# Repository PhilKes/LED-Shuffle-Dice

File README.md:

# LED Shuffle Dice
### Attiny85 with Shiftregister and Accelerometer
#### Parts
* Attiny85 Microcontroller
* **74HC595** Shiftregister
* 7 **Red LEDs**
* Coin Cell Battery + Holder
* ADXL345 Accelerometer
#### Schematic

* Minimal I/O Pins required (in total: 4)
* 2 Pin Connection to Shiftregister (CLK and DATA to **Attiny85** + LATCH connected to DATA)
* Accelerometer for Shake Detection
* "Shuffle" Animation
* LEDs logically connected in Pairs

#### 3D Printed Case

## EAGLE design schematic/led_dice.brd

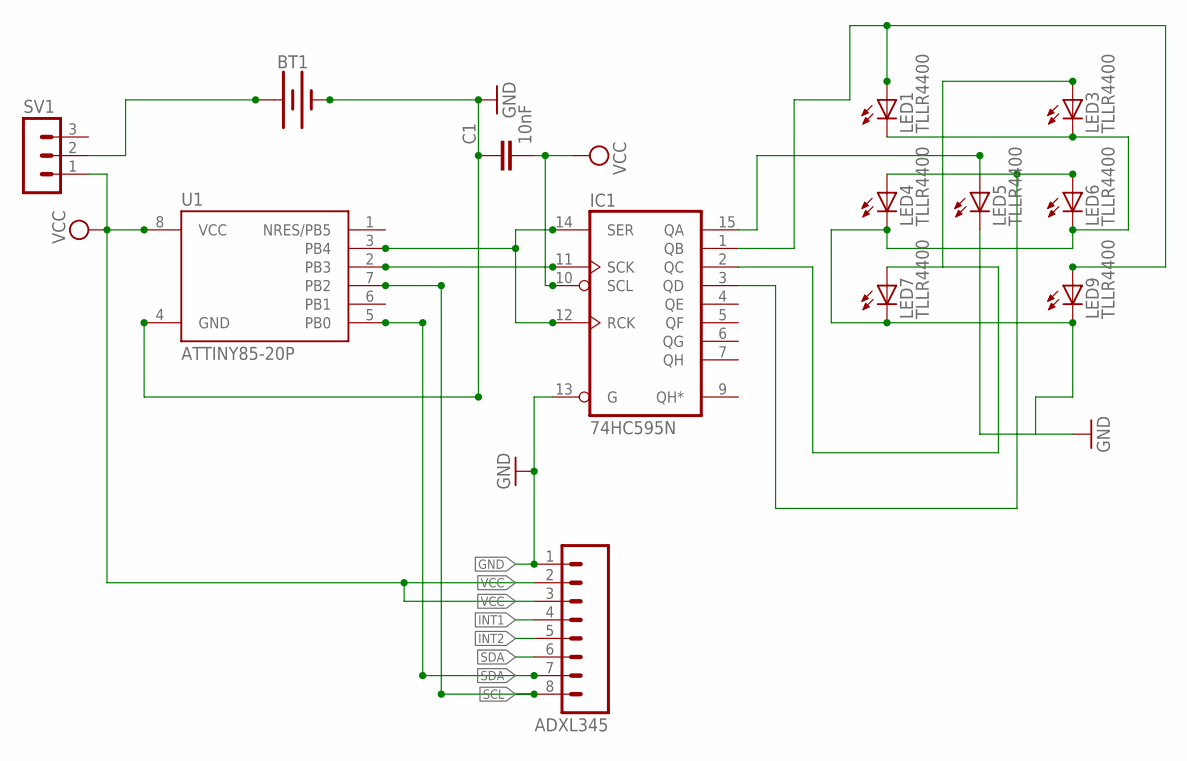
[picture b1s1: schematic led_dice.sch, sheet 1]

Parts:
ADXL345: M08; 1X08
BT1: BATTERY-20MM_PTH; BATTCOM_20MM_PTH
C1: 10nF; C025-024X044
IC1: 74HC595N; DIL16
LED1, LED3, LED4, LED5, LED6, LED7, LED9: TLLR4400; LED3MM
SV1: MA03-1
U1: ATTINY85-20P; PDIP08_300MIL

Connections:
GND: ADXL345.1, BT1.2 (-), C1.1, IC1.8 (GND), IC1.13 (G), LED1.K (C), LED3.K (C), LED4.K (C), LED5.K (C), LED6.K (C), LED7.K (C), LED9.K (C), U1.4 (GND)
INT1: ADXL345.4
INT2: ADXL345.5
unnamed: IC1.1 (QB), LED1.A, LED9.A
unnamed: IC1.15 (QA), LED5.A
unnamed: IC1.11 (SCK), U1.2 (PB3)
unnamed: IC1.3 (QD), LED4.A, LED6.A
unnamed: BT1.1 (+), SV1.2
unnamed: IC1.2 (QC), LED3.A, LED7.A
unnamed: IC1.12 (RCK), IC1.14 (SER), U1.3 (PB4)
SCL: ADXL345.8, U1.7 (PB2)
SDA: ADXL345.7, U1.5 (PB0)
VCC: ADXL345.2, ADXL345.3, C1.2, IC1.10 (SCL), IC1.16 (VCC), SV1.1, U1.8 (VCC)

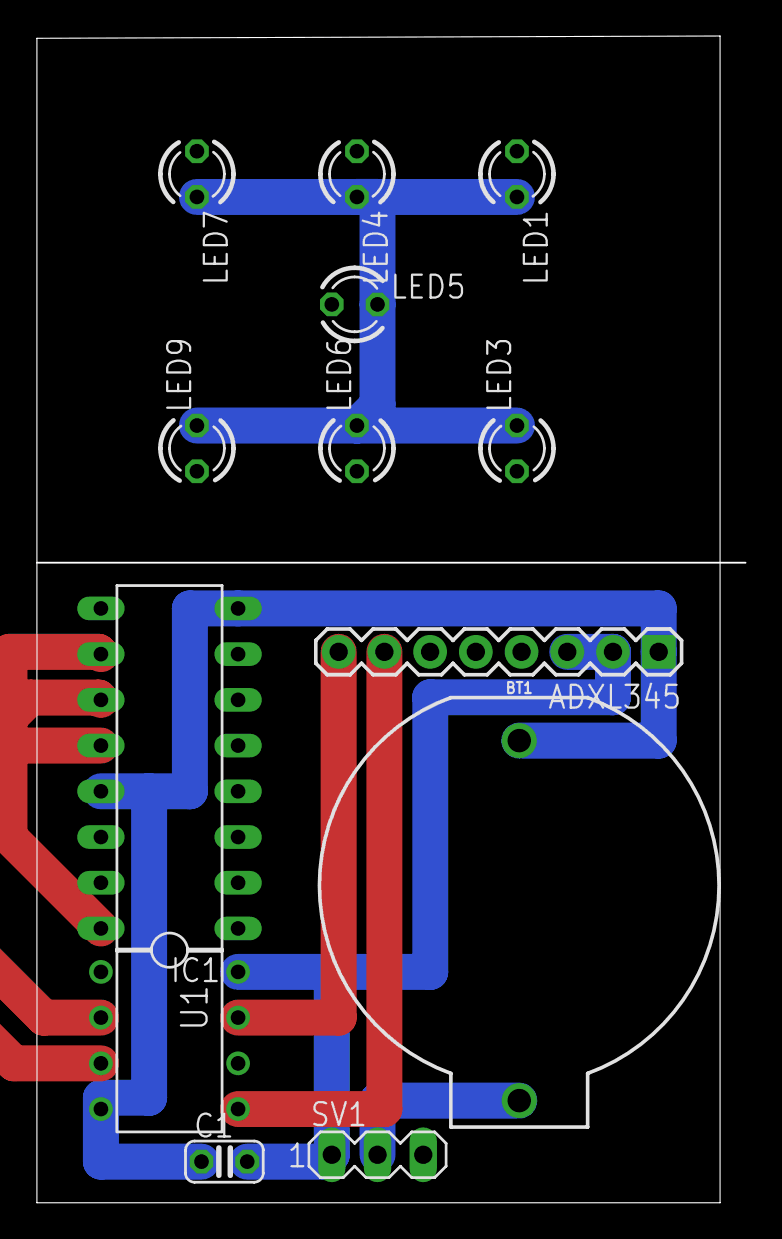
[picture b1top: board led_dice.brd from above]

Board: 2 copper layers, 39.4 x 64.7 mm, 13 parts (0 on the bottom side), 11 nets.

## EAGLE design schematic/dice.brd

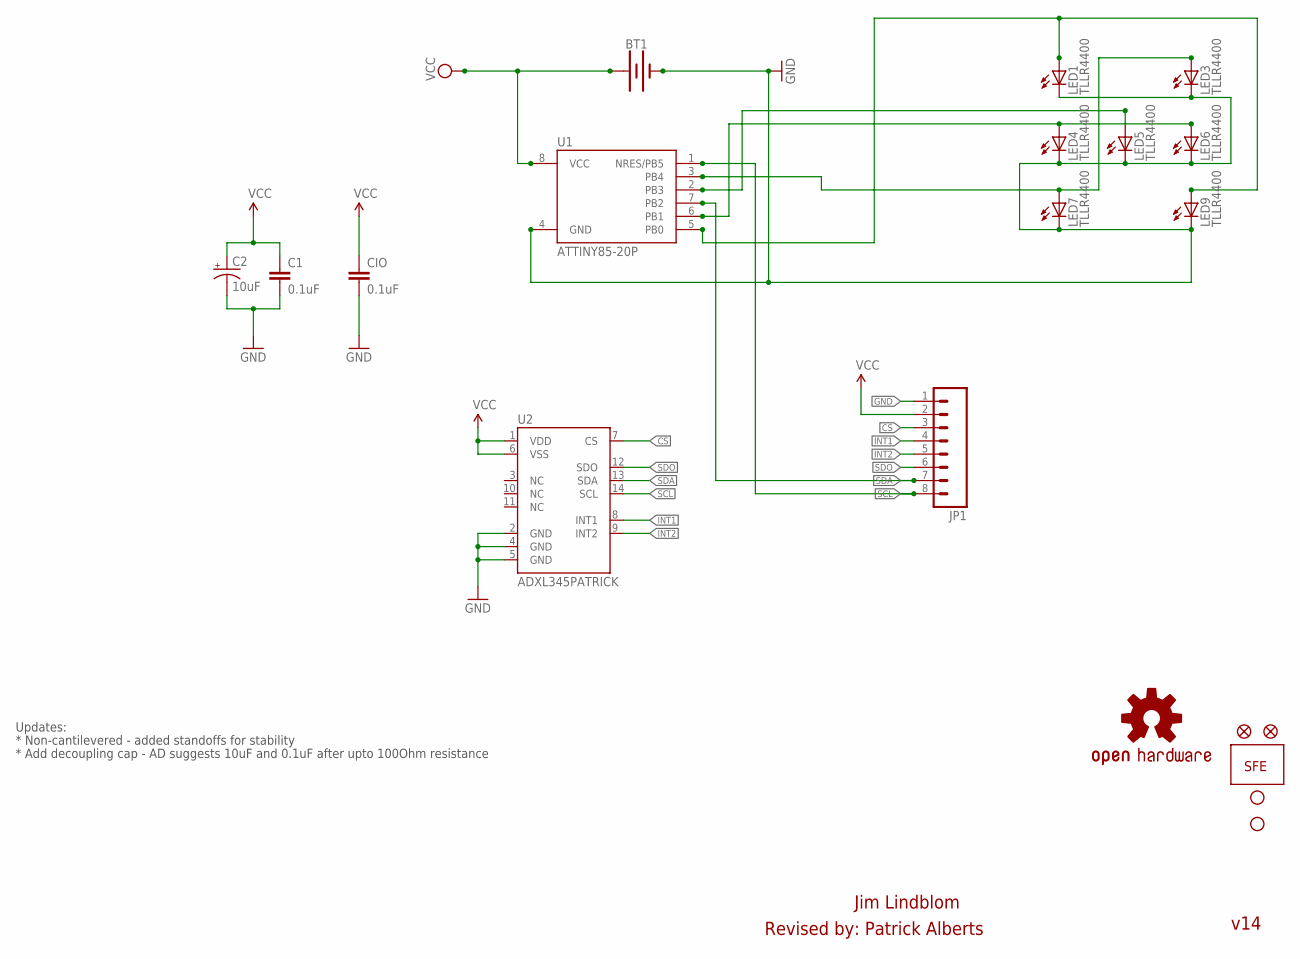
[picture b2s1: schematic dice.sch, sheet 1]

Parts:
BT1: BATTERY-20MM_PTH; BATTCOM_20MM_PTH
C1: 0.1uF; 0603-CAP
C2: 10uF; EIA3216
CIO: 0.1uF; 0603-CAP
JP1: M08; 1X08
JP2, JP3: STAND-OFF
JP4, JP5: FIDUCIAL1X2; FIDUCIAL-1X2
LED1, LED3, LED4, LED5, LED6, LED7, LED9: TLLR4400; LED3MM
U1: ATTINY85-20P; PDIP08_300MIL
U2: ADXL345PATRICK; LGA14_1:1_PATRICK
U$2: LOGO-SFENEW; SFE-NEW-WEBLOGO
U$3: OSHW-LOGOS; OSHW-LOGO-S

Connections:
CS: JP1.3, U2.7 (CS)
GND: BT1.2 (-), C1.2, C2.C (-), CIO.2, JP1.1, LED1.K (C), LED3.K (C), LED4.K (C), LED5.K (C), LED6.K (C), LED7.K (C), LED9.K (C), U1.4 (GND), U2.2 (GND), U2.4 (GND), U2.5 (GND)
INT1: JP1.4, U2.8 (INT1)
INT2: JP1.5, U2.9 (INT2)
unnamed: LED1.A, LED9.A, U1.5 (PB0)
unnamed: LED3.A, LED7.A, U1.3 (PB4)
unnamed: LED5.A, U1.2 (PB3)
unnamed: LED4.A, LED6.A, U1.6 (PB1)
SCL: JP1.8, U1.1 (NRES/PB5), U2.14 (SCL)
SDA: JP1.7, U1.7 (PB2), U2.13 (SDA)
SDO: JP1.6, U2.12 (SDO)
VCC: BT1.1 (+), C1.1, C2.A (+), CIO.1, JP1.2, U1.8 (VCC), U2.1 (VDD), U2.6 (VSS)

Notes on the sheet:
Updates:
* Non-cantilevered - added standoffs for stability
* Add decoupling cap - AD suggests 10uF and 0.1uF after upto 100Ohm resistance
Jim Lindblom
Revised by: Patrick Alberts
v14

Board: 2 copper layers, 20 parts (0 on the bottom side), 12 nets, no tracks yet.

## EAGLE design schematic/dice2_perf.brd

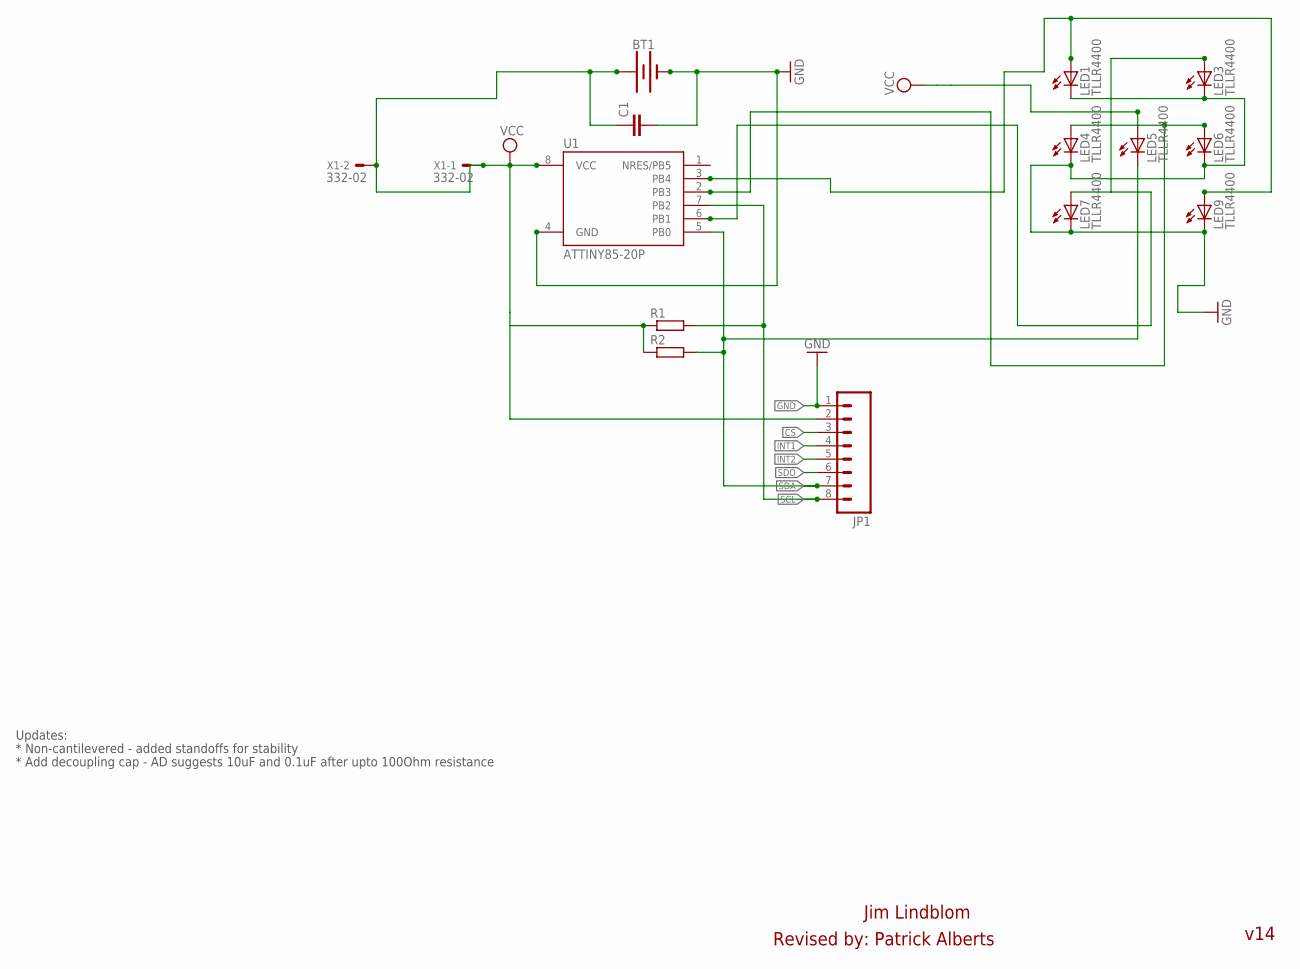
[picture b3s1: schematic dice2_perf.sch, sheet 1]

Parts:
BT1: BATTERY-20MM_PTH; BATTCOM_20MM_PTH
C1: C-EU025-024X044; C025-024X044
JP1: M08; 1X08
LED1, LED3, LED4, LED5, LED6, LED7, LED9: TLLR4400; LED3MM
R1: R-EU_0207/12; 0207/12
R2: R-EU_0207/2V; 0207/2V
U1: ATTINY85-20P; PDIP08_300MIL
X1: 332-02

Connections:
CS: JP1.3
GND: BT1.2 (-), C1.2, JP1.1, LED1.K (C), LED3.K (C), LED4.K (C), LED6.K (C), LED7.K (C), LED9.K (C), U1.4 (GND)
INT1: JP1.4
INT2: JP1.5
unnamed: LED1.A, LED9.A, U1.3 (PB4)
unnamed: LED4.A, LED6.A, U1.2 (PB3)
unnamed: LED3.A, LED7.A, U1.6 (PB1)
SCL: JP1.8, R1.2, U1.7 (PB2)
SDA: JP1.7, LED5.K (C), R2.2, U1.5 (PB0)
SDO: JP1.6
VCC: BT1.1 (+), C1.1, JP1.2, LED5.A, R1.1, R2.1, U1.8 (VCC), X1.1, X1.2

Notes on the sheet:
Updates:
* Non-cantilevered - added standoffs for stability
* Add decoupling cap - AD suggests 10uF and 0.1uF after upto 100Ohm resistance
Jim Lindblom
Revised by: Patrick Alberts
v14

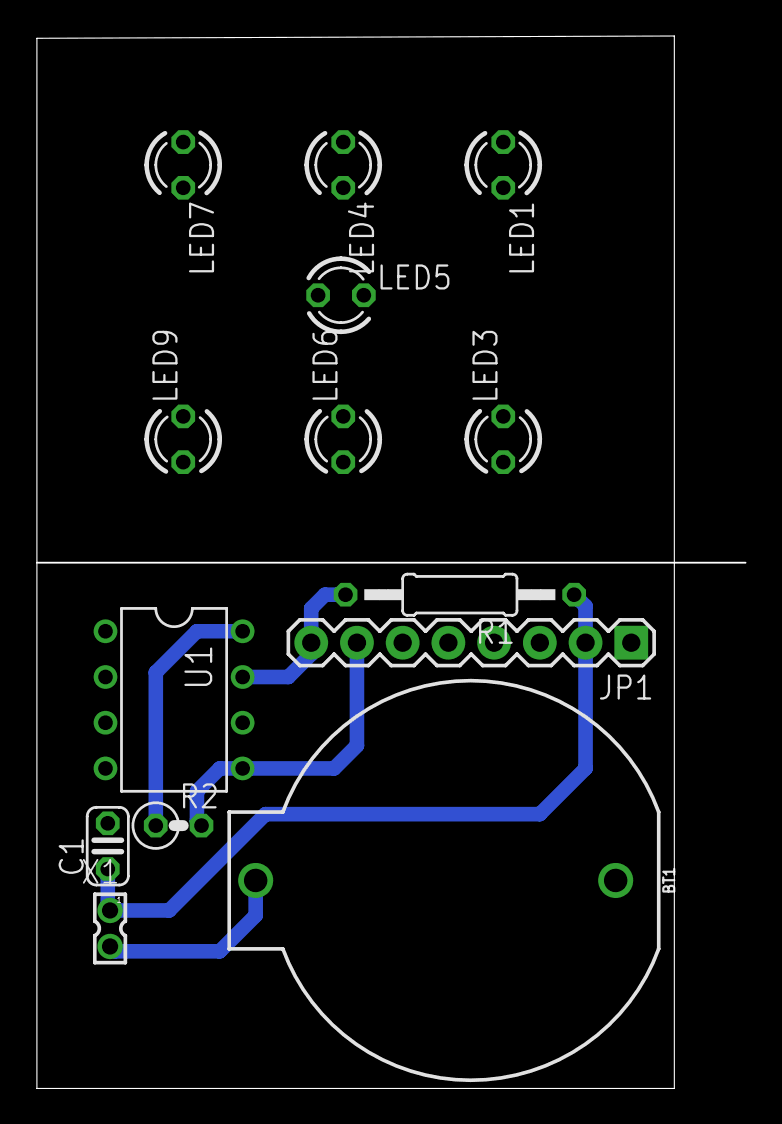
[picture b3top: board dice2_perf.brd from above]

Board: 2 copper layers, 39.4 x 58.4 mm, 14 parts (0 on the bottom side), 7 nets.

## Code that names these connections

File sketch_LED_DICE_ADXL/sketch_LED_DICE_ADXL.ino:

// https://github.com/PhilKes/LED_Roll_Dice
// Attiny85 + 74HC595 + ADXL345
#include <TinyWireM.h>
#include <avr/power.h>

#define ROLL_THRESHOLD  16

float x, y, z;

int dataPin = PB4;
int clockPin = PB3;

/*
   Attiny - 74hc595
   PB3 - SHCP (Clock)
   PB4 - DS (Data) + STCP (Latch)
   VCC - MR
   GND - OE

   Attiny - ADXL345
   VCC - CS
   PB0 - SDA
   PB2 - SCL
*/


void setup ()
{
  pinMode(clockPin, OUTPUT);
  pinMode(dataPin, OUTPUT);
  digitalWrite(dataPin, 0);
  digitalWrite(clockPin, 0);
  randomSeed(analogRead(0));
  // Setup ADXL345
  adxl345_init();
  setLeds(0);
}

float X, Y, Z, totalAccel;

void loop()
{

  //rollDice();
  //delay(2000);

  /* for (int i = 1; i < 7; i++) {
     setLeds(i);
     delay(2000);
    }*/

  X = 0;
  Y = 0;
  Z = 0;
  for (int i = 0; i < 10; i++) {
    readAccel(&x, &y, &z);
    X += x;
    Y += y;
    Z += z;
    delay(1);
  }
  X /= 10;
  Y /= 10;
  Z /= 10;

  totalAccel = sqrt(X * X + Y * Y + Z * Z);
  if (totalAccel > ROLL_THRESHOLD) {
    delay(150);
    // Shuffle Effect
    int last = 1;
    int next = 1;
    for (int i = 0; i < 5; i++) {
      while (next == last)
        next = random(1, 7);
      last = next;
      setLeds(next);
      delay(200);
    }
    rollDice();
    delay(1700);
  }

}

byte leds = 0;
void setLeds(int number) {
  if (number == 0) {
    leds = 0;
  }
  else if (number == 1) {
    leds = B00000001;
  }
  else if (number == 2) {
    leds = B00000010;
  }
  else if (number == 3) {
    leds = B00000011;
  }
  else if (number == 4) {
    leds = B00000110;
  }
  else if (number == 5) {
    leds = B00000111;
  }
  else if (number == 6) {
    leds = B00001110;
  }
  //shiftLeds(leds);
  shiftOut(dataPin, clockPin, MSBFIRST, leds);
  digitalWrite(clockPin, 0);
  //latch with dataPin
  digitalWrite(dataPin, 0);
  delay(10);
  digitalWrite(dataPin, 1);
  delay(10);
  digitalWrite(dataPin, 0);
}

void rollDice() {
  setLeds( random(1, 7));
}

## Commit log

2020-08-15 initial sketches, schematic, case added
2020-08-20 case: 123Design case added + Sketch updates
2020-08-24 Using dataPin for Shift Register LATCH
2020-08-29 ADXL345 Shake detection added to Sketch + Schematic updated
2020-08-29 FFT fixes
2020-08-30 Schematic fixes
2020-09-03 Sketch: added Shuffle Effect + 3d case updated
2020-09-03 3D Case fixes
2021-05-26 Fusion 360 2-part case .STL Files added
2021-05-26 added doc/shuffle.gif

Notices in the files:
parts and their libraries:
SparkFun-Batteries: Licensing: Creative Commons ShareAlike 4.0 International - https://creativecommons.org/licenses/by-sa/4.0
SparkFun-Aesthetics: Licensing: CC v3.0 Share-Alike You are welcome to use this library for commercial purposes.
SparkFun-Aesthetics: Released under the Creative Commons
